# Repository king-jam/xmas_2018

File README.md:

# xmas_2018

Chrismas Cards for 2018

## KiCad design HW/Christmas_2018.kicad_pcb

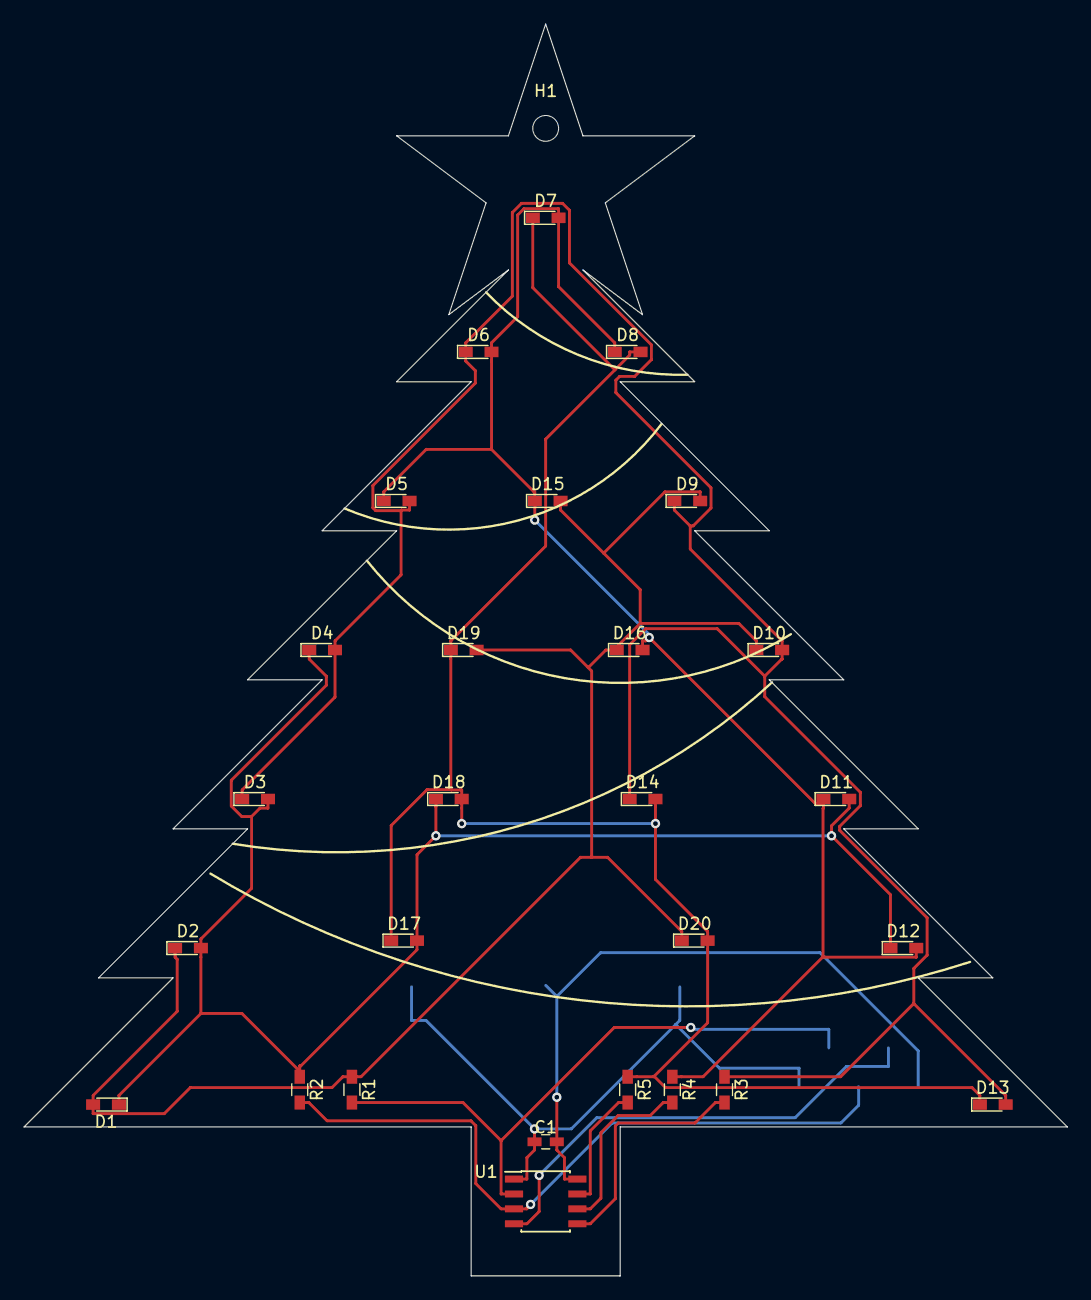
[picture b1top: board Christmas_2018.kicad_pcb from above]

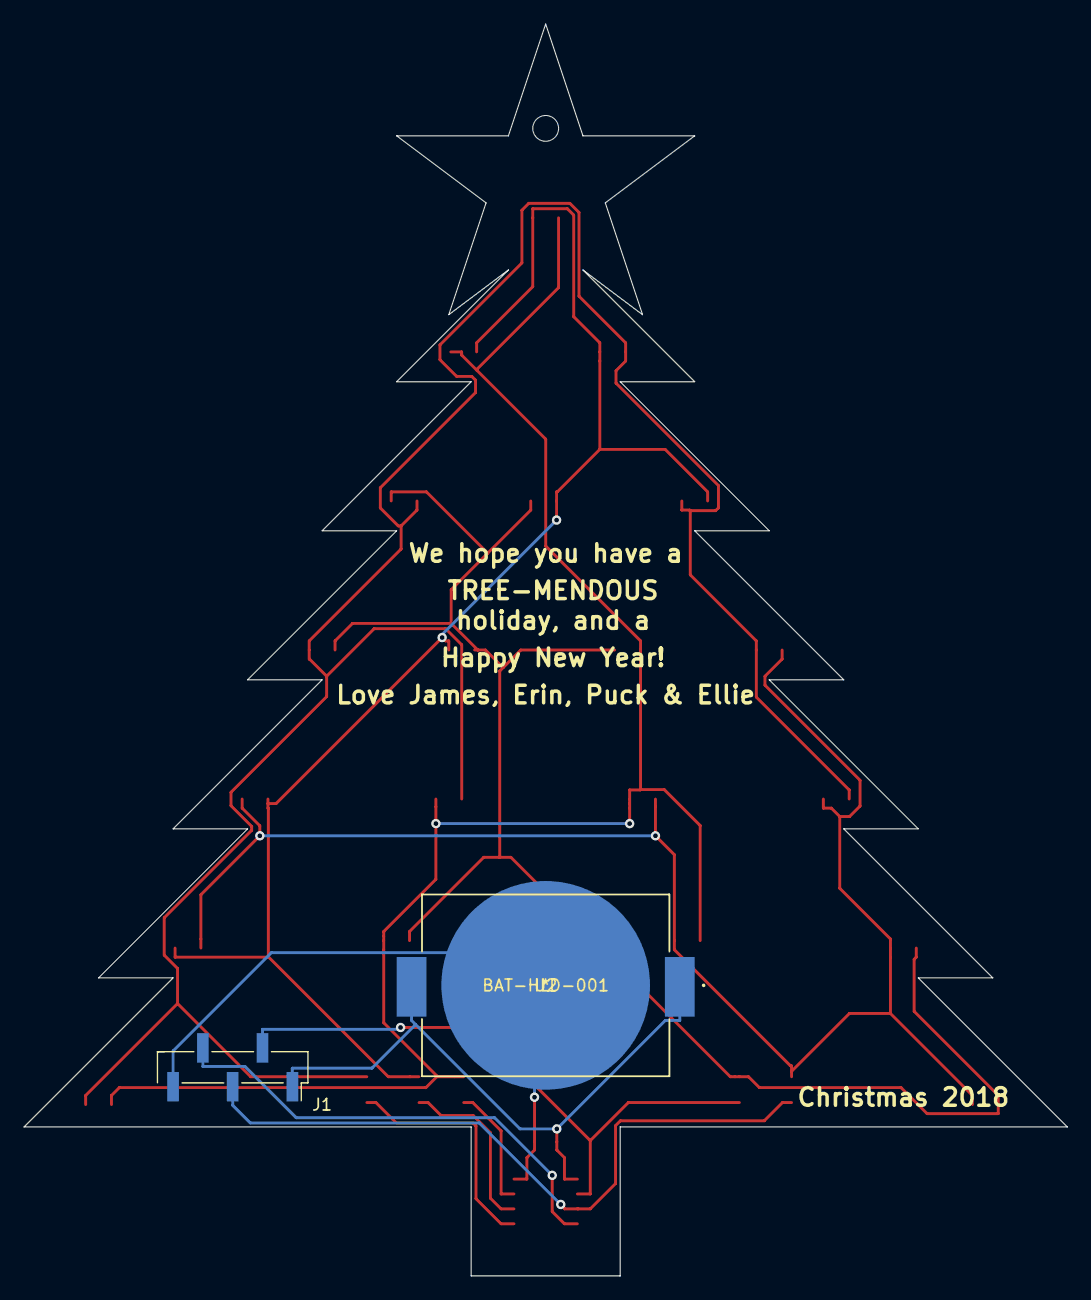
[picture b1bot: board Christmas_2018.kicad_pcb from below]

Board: 2 copper layers, 88.9 x 106.7 mm, 30 parts (2 on the bottom side), 13 nets.

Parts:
C1: 100nF; C_0603_HandSoldering
D1, D2, D3, D4, D5, D6, D7, D8, D9, D10, D11, D12, D13, D14, D15, D16, D17, D18, D19, D20: LED; LED_0603_HandSoldering
H1: MountingHole; MountingHole_2.2mm_M2
J1: Conn_01x05_Male; Pin_Header_Straight_1x05_Pitch2.54mm_SMD_Pin1Right
R1, R2, R3, R4, R5: 0; R_0603_HandSoldering
U1: ATtiny102-SSNR; SOIC-8_3.9x4.9mm_Pitch1.27mm
U2: BAT-HLD-001

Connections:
/PA0: J1.2, R1.2, U1.2
/PA1: J1.3, R2.2, U1.3
/PB1: R3.2, U1.5
/PB2: R4.2, U1.6
/PB3: R5.2, U1.7
/RST: J1.4, U1.4
GND: C1.2, J1.5, U1.8, U2.2
unnamed: D1.1, D2.2, D3.2, D4.1, D11.2, D12.1, D17.2, D18.1, R2.1
unnamed: D1.2, D2.1, D9.2, D10.1, D15.2, D16.1, D19.2, D20.1, R1.1
unnamed: D3.1, D4.2, D5.2, D6.1, D9.1, D10.2, D13.2, D14.1, R3.1
unnamed: D5.1, D6.2, D7.2, D8.1, D11.1, D12.2, D15.1, D16.2, R4.1
unnamed: D7.1, D8.2, D13.1, D14.2, D17.1, D18.2, D19.1, D20.2, R5.1
VCC: C1.1, J1.1, U1.1, U2.1, U2.3

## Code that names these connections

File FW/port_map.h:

#ifndef PORT_MAP_H_
#define PORT_MAP_H_

#include <avr/pgmspace.h>

#define PA0_OFFSET 0 // Pin 2 (PA0) on ATtiny102
#define PA1_OFFSET 1 // Pin 3 (PA1) on ATtiny102
#define PB1_OFFSET 2 // Pin 5 (PB1) on ATtiny102
#define PB2_OFFSET 3 // Pin 6 (PB2) on ATtiny102
#define PB3_OFFSET 4 // Pin 7 (PB3) on ATtiny102

#define PA_MASK 0x03	// mask to just get the PA components
#define PA_RS 0			// right shift value to align with PORTA/DDRA positions
#define PB_MASK 0x1C	// mask to just get the PB components
#define PB_RS 1			// right shift value to align with PORTB/DDRB positions

//direction config for each LED (1 = output)
const unsigned char led_port_dir[20] PROGMEM = {
	( 1 << PA0_OFFSET | 1 << PA1_OFFSET ), // D1
	( 1 << PA0_OFFSET | 1 << PA1_OFFSET ), // D2
	( 1 << PA1_OFFSET | 1 << PB1_OFFSET ), // D3
	( 1 << PA1_OFFSET | 1 << PB1_OFFSET ), // D4
	( 1 << PB1_OFFSET | 1 << PB2_OFFSET ), // D5

	( 1 << PB1_OFFSET | 1 << PB2_OFFSET ), // D6
	( 1 << PB2_OFFSET | 1 << PB3_OFFSET ), // D7
	( 1 << PB2_OFFSET | 1 << PB3_OFFSET ), // D8
	( 1 << PA0_OFFSET | 1 << PB1_OFFSET ), // D9
	( 1 << PA0_OFFSET | 1 << PB1_OFFSET ), // D10

	( 1 << PA1_OFFSET | 1 << PB2_OFFSET ), // D11
	( 1 << PA1_OFFSET | 1 << PB2_OFFSET ), // D12
	( 1 << PB1_OFFSET | 1 << PB3_OFFSET ), // D13
	( 1 << PB1_OFFSET | 1 << PB3_OFFSET ), // D14
	( 1 << PA0_OFFSET | 1 << PB2_OFFSET ), // D15

	( 1 << PA0_OFFSET | 1 << PB2_OFFSET ), // D16
	( 1 << PA1_OFFSET | 1 << PB3_OFFSET ), // D17
	( 1 << PA1_OFFSET | 1 << PB3_OFFSET ), // D18
	( 1 << PA0_OFFSET | 1 << PB3_OFFSET ), // D19
	( 1 << PA0_OFFSET | 1 << PB3_OFFSET ) //  D20
};

//output config for each LED (1 = High, 0 = Low)
const unsigned char led_port_lvl[20] PROGMEM = {
	( 1 << PA0_OFFSET ), // D1
	( 1 << PA1_OFFSET ), // D2
	( 1 << PA1_OFFSET ), // D3
	( 1 << PB1_OFFSET ), // D4
	( 1 << PB1_OFFSET ), // D5

	( 1 << PB2_OFFSET ), // D6
	( 1 << PB2_OFFSET ), // D7
	( 1 << PB3_OFFSET ), // D8
	( 1 << PA0_OFFSET ), // D9
	( 1 << PB1_OFFSET ), // D10

	( 1 << PA1_OFFSET ), // D11
	( 1 << PB2_OFFSET ), // D12
	( 1 << PB1_OFFSET ), // D13
	( 1 << PB3_OFFSET ), // D14
	( 1 << PA0_OFFSET ), // D15

	( 1 << PB2_OFFSET ), // D16
	( 1 << PA1_OFFSET ), // D17
	( 1 << PB3_OFFSET ), // D18
	( 1 << PA0_OFFSET ), // D19
	( 1 << PB3_OFFSET ) // D20
};

#endif /* PORT_MAP_H_ */

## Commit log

2018-11-28 Rev A. HW & Initial FW Support
2018-12-05 Debugging with a scope
2018-12-08 Moved to one nice LED since HW issues
2018-12-08 Cleanup
2018-12-08 Attributing sources
2018-12-08 Code comments and cleanup

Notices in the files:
parts and their libraries:
Copyright 2016 Accelerated Designs. All rights reserved.
